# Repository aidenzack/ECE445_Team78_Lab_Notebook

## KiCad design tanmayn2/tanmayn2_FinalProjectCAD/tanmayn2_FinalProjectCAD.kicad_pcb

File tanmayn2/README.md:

## **Tanmay's Worklog**

### Week of 2026-02-18 - System Architecture Layout
Early planning of our system established design constraints we wanted to stick to, such as 
having 2 seperate USB-C connections:
- MCU (Arduino Nano ESP32) for 5V power and UART connection
- Battery Charging as part of our custom power management system to produce 3.3V power for peripherals

Which IMU we went with was based on high precision, tolerance for high-speed (up to 2000 degrees/sec motions) and force,
and SPI communication. This led us to choosing the:

**Adafruit TDK InvenSense ICM-20948 IMU**

Synchronization across all 4 sensors (Placed at the wrist, elbow, hip, and knee to capture the full kinematic chain) is key so we intend
to set up an FSYNC, with our fall back being that we can increase our sampling rate.

**Timing Analysis:**

- With a sampling rate of 200 Hz, we have a period _T_ = 5 ms.
- Our IMUs have an approximate read time of ~0.1ms
- Even during the fastest movements such as a wrist flick (~30 ms), we can capture 5-6 samples and grab precise data.

### Weeks of 2026-02-25 & 2026-03-02 - Full PCB Schematic Finalized + 1st Round PCB Ordered

I completed the first revision of our PCB Schematic and design, involving the following components:

- USB-C Receptacle (Power Input)
- Charger + Power Path IC (BQ24074RGT)
- 3.3V, 500mA LDO (TLV75533PDBVR)
- Arduino Nano ESP32
- Headers for Li-Po battery, IMUs
- LEDs for Debugging
- Designed 8-pin JST-style connectors for each IMU
- Implemented:
  - **Series resistors (22–47 Ω)** on SPI lines
  - **ESD protection** at connectors
  - **Local decoupling** at each connector

***PCB Schematic (Revision A)***

After the PCB Design Review, we talked with our TA about whether or not we are allowed to implement the full Arduino Nano ESP32 devboard or only allowed to use the chip.

Result - Allowed to use full Arduino Nano ESP32 Dev Board (w/ USB-C port, RESET button). Our PCB will be designed as expansion board for the MCU

---

### Week of 2026-03-08 - Tolerance Analysis of SPI Bus and Cable Delay

### SPI Throughput & Utilization Analysis

_Assumptions_

- 4 IMUs (wrist, elbow, hip, knee)
- Sampling rate: **220 Hz**
- Data per sample:
  - Accelerometer: 6 bytes
  - Gyroscope: 6 bytes
  - Register overhead: 1 byte

**Total per sample:**

```
13 bytes / sample / IMU
```

### Total Data Rate

```
13 bytes × 4 IMUs × 220 Hz = 11,400 bytes/s
11,440 × 8                  = 91,520 bits/s
```

### SPI Bus Capacity (2 MHz)

```
2,000,000 bits/s ÷ 8 = 250,000 bytes/s
```

### Bus Utilization

```
91,520 / 2,000,000 = 4.576%
```

### Interpretation

- Only **~4.576%** SPI bus utilization
- System is far from bandwidth-limited
- Allows operation at a **reduced SPI clock for robustness**

### SPI Timing & Cable Delay Analysis

### SPI Clock

Selected SPI clock: **2 MHz**

```
T            = 1 / 2 MHz = 500 ns
Half-cycle   = 250 ns
```

### Cable Length Estimates

| Sensor | Length (m) |
| :----- | :--------- |
| Wrist  | 1.00       |
| Elbow  | 0.45       |
| Hip    | 0.60       |
| Knee   | 0.90       |

### Propagation Delay (≈ 5 ns/m)

**One-way delay:**

```
t_pd = 5 ns/m × L
```

| Sensor | Delay (ns) |
| :----- | :--------- |
| Wrist  | 5.00       |
| Elbow  | 2.25       |
| Hip    | 3.00       |
| Knee   | 4.50       |

**Round-trip delay:**

```
t_rt ≈ 2 × t_pd
```

| Sensor | Delay (ns) |
| :----- | :--------- |
| Wrist  | 10.0       |
| Elbow  | 4.5        |
| Hip    | 6.0        |
| Knee   | 9.0        |

### Timing Comparison (Worst Case — Wrist)

```
One-way    : 5 ns  / 250 ns = 2.0%
Round-trip : 10 ns / 250 ns = 4.0%
```

### Interpretation

- Cable delay is **small relative to the SPI timing budget**
- 2 MHz provides **comfortable timing margin**
- System remains robust despite off-board wiring

---
## Week of 2026-03-08 - Testing and Validation
 
The entire signal chain was validated on a breadboard. This allowed us to verify SPI bus integrity and IMU synchronization in parallel with PCB fabrication.
 
### Breadboard Setup
 
The breadboard mirrors the central PCB topology:
 
- 1 × Arduino Nano ESP32 (MCU)
- 4 × ICM-20948 IMU breakout boards (wrist, elbow, hip, knee positions)
- Shared SPI bus: `SCLK`, `MOSI`, `MISO`
- Independent `CS_<IMU>` lines per IMU
- Shared `FSYNC` line (driven directly at 3.3 V on breadboard for testing)
> Built in collaboration with my teammate's Arduino firmware to read all 4 IMUs across the shared SPI bus.

**_Breadboard Setup_**

### Test 1 — SPI Bus Synchronization
 
**Goal:** Verify that the MCU correctly reads all 4 IMUs across the shared SPI bus within a single sampling frame, and that each IMU is uniquely identifiable via its `CS` line.
 
**Method:** Since all 4 IMUs are physically located on the same plane on the breadboard, their accelerometer and gyroscope readings should be **closely aligned** at any given instant — both at rest and under shared motion.

**_Breadboard Setup at Rest_**

**_Breadboard Setup in Motion_**

- The `Δ` values represent **sequential read delay** on the SPI bus, **not** sampling-time difference between IMUs.

### Test 2 — FSYNC Clock Alignment
 
**Goal:** Verify that the shared `FSYNC` line successfully aligns the internal sampling clocks of all 4 IMUs to a common reference.
 
**Method:** The firmware waits for the data-ready condition on all 4 IMUs, then assigns a shared frame number. By tracking the **frame index of peak motion** for each IMU, we can detect whether the IMUs' internal clocks are drifting independently or marching in lockstep.
 
**Before FSYNC Trigger (at rest, clocks free-running):**

> Peak-motion frames are **scattered** across IMU1=1, IMU2=32, IMU3=72, IMU4=34 — the internal sampling clocks are running independently.
 
**After FSYNC Trigger (sharp flick of breadboard provides impulse):**

> All 4 IMUs report peak motion at the **same frame index (2266)** — the FSYNC impulse successfully aligned their internal clocks.
---
## Week of 2026-03-23 - PCB Revisions

At the onset of delivery of our 1st Round PCB order, several issues were identified that required revisions before fabrication of our final design.
 
### Battery Connector Footprint Mismatch
 
- **Issue:** The Adafruit 3.7 V 1200 mAh Li-Po battery ships with **JST-PH 2.00 mm** connectors.
- **Original footprint:** Molex KK-254 **2.54 mm** male headers.
- **Resolution:** Updated the Li-Po battery connector footprint on the PCB to match JST-PH 2.00 mm.
### Trace Width Revisions for Power Signals
 
Several power-carrying traces needed to be widened to safely handle higher current loads:
 
| Signal      | Path                              | Old Width | New Width |
| :---------- | :-------------------------------- | :-------- | :-------- |
| `VDD5V`     | USB-C input → Charger IC          | 10 mils   | 20 mils   |
| `VBAT`      | Charger IC → Li-Po battery        | 10 mils   | 20 mils   |
| `+3V3_MAIN` | LDO → 4 IMUs + debugging LED      | 10 mils   | 20 mils   |

### FSYNC Logic-Level Mismatch
 
**Issue:** Per the Adafruit TDK InvenSense **ICM-20948** datasheet, the `FSYNC` pin requires an approximate **1.8 V** logic input. However, the Arduino Nano ESP32's `FSYNC` GPIO drives at **3.3 V**, ruling out a direct connection.
 
**Resolution:** Designed a **resistor voltage divider** to step down the 3.3 V signal to ~1.8 V before feeding it to the IMUs.

Used Resistors 2.2kΩ and 1.91kΩ as per ECE Shop availability

**Calculation:**
```
FSYNC_B = 3.3 V
 
FSYNC = FSYNC_B × ( 2.2 kΩ / (1.91 kΩ + 2.2 kΩ) )
      = 3.3 V × (2.2 / 1.91 + 2.2)
      = 1.767 V ~ 1.8V
```

**_Resistor Network for Stepdown to FSYNC_**

**_FINALIZED PCB DESIGN_**

---

## Week of 2026-03-30 - Initial Python Implementation

- Set up Python implementation via Spyder to process serial SPI data, set up initial zero calibration, capture accelerometer and gyroscope data from all 4 IMUs using hard triggers (START, STOP), and plot accelerometer and gyroscope data across all axes and for the IMU of the user's choosing.
- Extended and expanded upon heading into the week of 2026-04-06 in preparation for Progress Demo

---

## Week of 2026-04-06 - Progress Demo

- Set up end-to-end implementation from validating IMU connection to microcontroller via a healthy SPI bus, performed zero-calibration and proving effects of FSYNC on sample collection, and post-processing and data depiction through our Spyder implementation.
- Professor Joohyung Kim approved of the software backend and expected us to expand on it for interpretability and ease of operation, yet wanted to ensure our final on-body implementation can ensure the same functionality, especially with cable runs and promoting signal integrity to/from IMUs.

---

## Week of 2026-04-13 - Begin PCB Soldering

- With our finalized PCB finally delivered and our software implementation in a good spot, we began soldering our PCB. We used the oven to solder on most of the components, aside from the connectors, and afterwards, verified trace connections by using the continuity function on the multimeter
- Certain adjustments needed to be made. For instance, the ENABLE pin of the LDO was currently floating due to a mistake we made on the tracing side. We fixed this by soldering on a breadboard wire and tying the VSYS signal to the ENABLE pin, bringing it up to HIGH whenever the system is on and ensuring our LDO is actually working.
- Another issue was where our USB-C was positioned on our board. We realized we needed to cut out part of the ground plane and create a notch for the USB-C cable to connect through. After working with the machine shop, we got it fixed.
- From here, we wanted to check signal integrity from the PCB to the off-board IMUs via continuity mode and voltage readings when powered on.

**_PCB Probing_**

---

## Week of 2026-04-20 - Mock Demo + Presentation

- After finalizing PCB functionality and set up cable connections to IMUs, we set out to finalize on-body implementation and refine our software. We did the following:
  - CAD'ed and 3D-printed enclosures for the PCB and IMUs
  - Crafted straps for IMUs to sit on and to wear on the body
  - Crafted chest brace for PCB
  - Connected the entire PCB-IMU system to one of our teammates (Arjun)
  - Switched our Python implementation over to Dash Plotly
  - Implemented trigger-based Start (knee dip) and Stop (Wrist flick) shot capture mechanic into Python code

 **_UI Dashboard_**

- Mingrui (TA) informed us that while everything looks good, we need to focus on implementing feedback and figure out that soon, as that is one of the more significant components of our project

---

## Week of 2026-04-27 - Final Demo + Presentation

- All components from last week were improved upon for greater functionality and security. This includes the following:
  - Changed from exposed, Dupont terminal crimp pins to 2.54mm pitch connector metal terminals and KF2510 housing connector for better functionality
  - Bolstered straps for IMUs and PCB to be less constricting yet more secure
  - **Implemented Feedback Mechanism into UI Dashboard**
    - Implemented High Pass Filter + Notch Filter to suppress noise over cable runs and strengthen integrity
    - Extracts peak gyroscope and accelerometer metrics along with timings between IMU peaks
    - Calculates over normal distribution in comparison to the success profile and assigns a "severity" score as to which issue is best to focus on

  - Added Shot Label Status with line of feedback, FG%, Last 20 Shots Improvement, and plot controls

---

## Final Demo Reflection

Overall, a solid implementation that represents what we aimed to do.

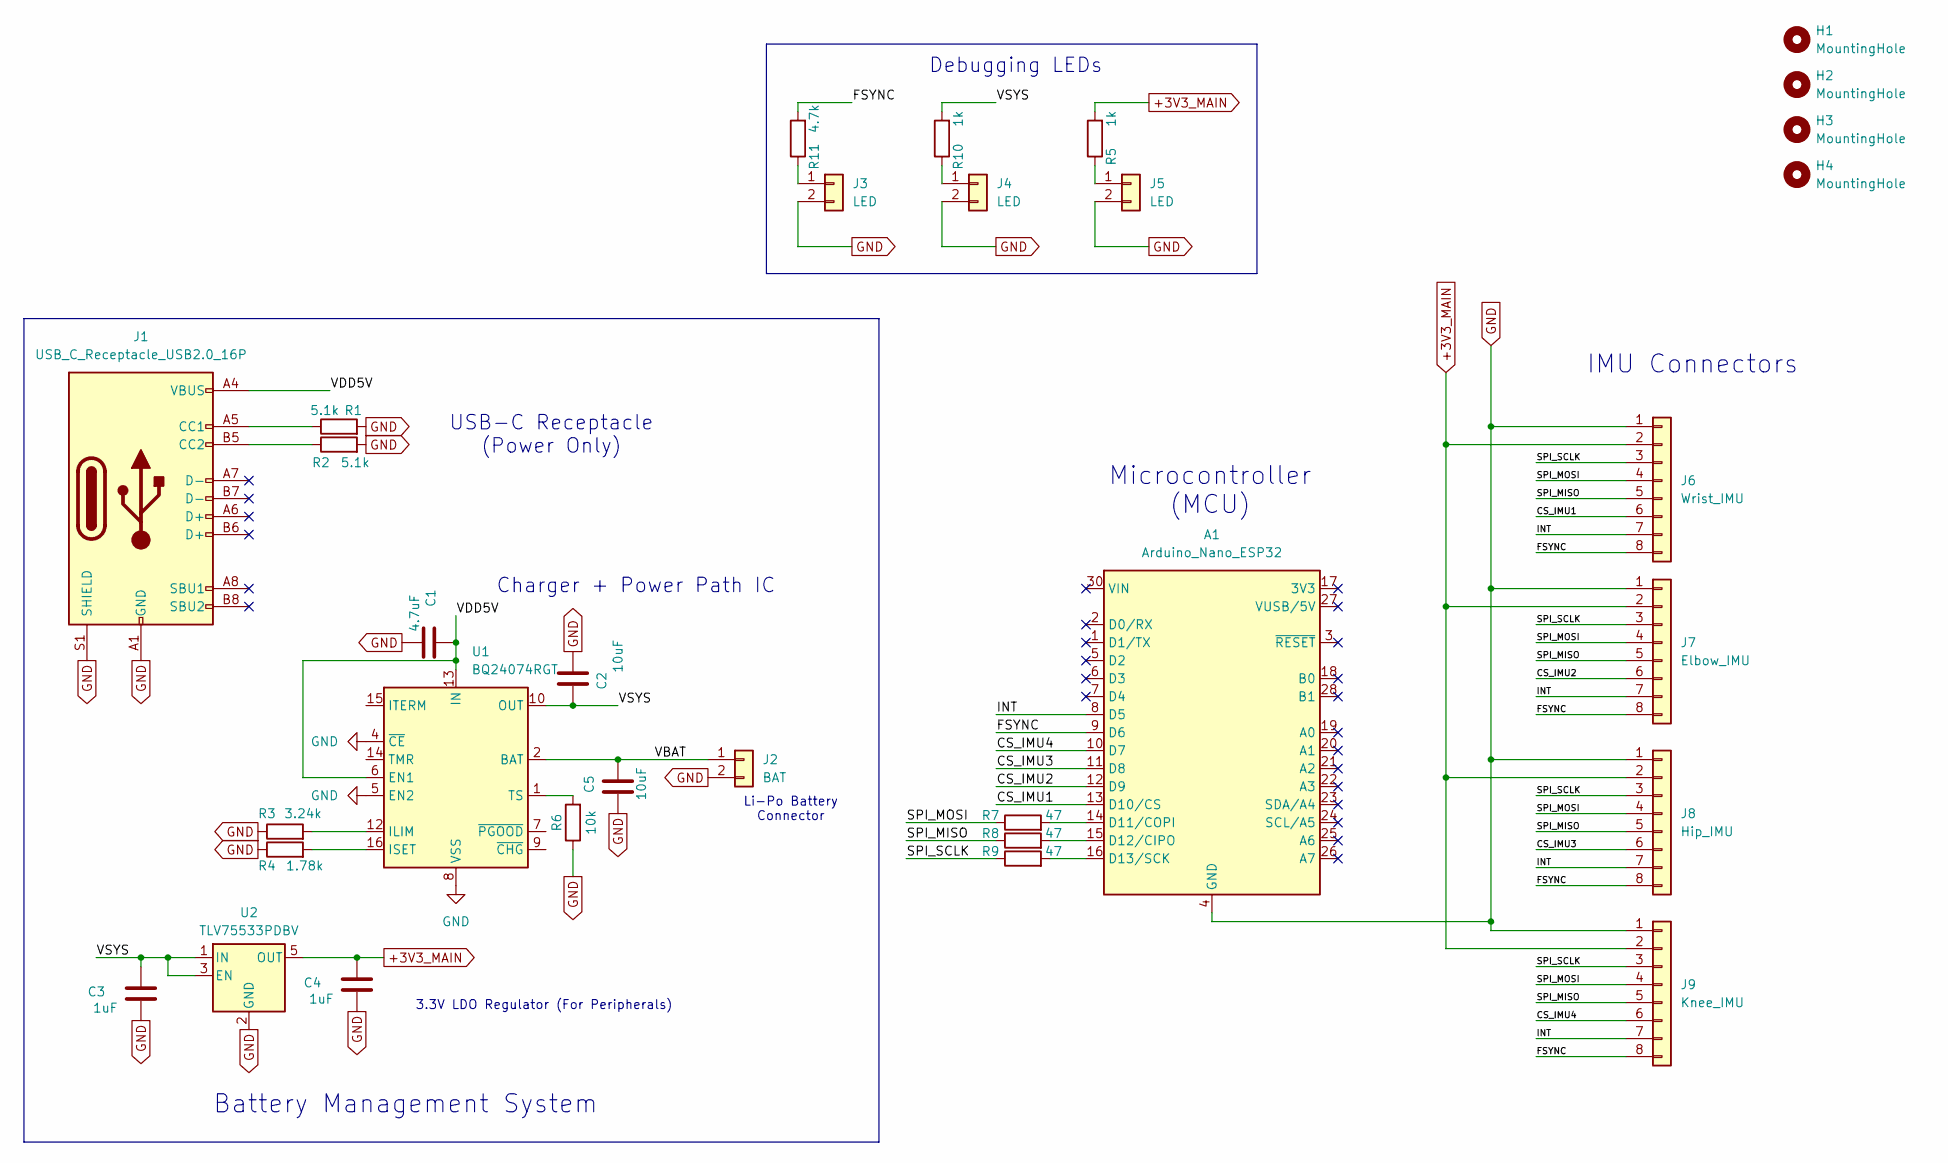
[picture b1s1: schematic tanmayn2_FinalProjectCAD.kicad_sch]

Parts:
A1: Arduino_Nano_ESP32; Arduino_Nano
C1: 4.7uF; C_0805_2012Metric_Pad1.18x1.45mm_HandSolder
C2, C5: 10uF; C_0805_2012Metric_Pad1.18x1.45mm_HandSolder
C3, C4: 1uF; C_0805_2012Metric_Pad1.18x1.45mm_HandSolder
H1, H2, H3, H4: MountingHole; MountingHole_3.2mm_M3
J1: USB_C_Receptacle_USB2.0_16P; USB_C_Receptacle_Molex_105450-0101
J2: BAT; Molex_KK-254_AE-6410-02A_1x02_P2.54mm_Vertical
J3, J4, J5: LED; Molex_KK-254_AE-6410-02A_1x02_P2.54mm_Vertical
J6: Wrist_IMU; Molex_KK-254_AE-6410-08A_1x08_P2.54mm_Vertical
J7: Elbow_IMU; Molex_KK-254_AE-6410-08A_1x08_P2.54mm_Vertical
J8: Hip_IMU; Molex_KK-254_AE-6410-08A_1x08_P2.54mm_Vertical
J9: Knee_IMU; Molex_KK-254_AE-6410-08A_1x08_P2.54mm_Vertical
R1, R2: 5.1k; R_0805_2012Metric_Pad1.20x1.40mm_HandSolder
R3: 3.24k; R_0805_2012Metric_Pad1.20x1.40mm_HandSolder
R4: 1.78k; R_0805_2012Metric_Pad1.20x1.40mm_HandSolder
R5, R10: 1k; R_0805_2012Metric_Pad1.20x1.40mm_HandSolder
R6: 10k; R_0805_2012Metric_Pad1.20x1.40mm_HandSolder
R7, R8, R9: 47; R_0805_2012Metric_Pad1.20x1.40mm_HandSolder
R11: 4.7k; R_0805_2012Metric_Pad1.20x1.40mm_HandSolder
U1: BQ24074RGT; VQFN-16-1EP_3x3mm_P0.5mm_EP1.6x1.6mm
U2: TLV75533PDBV; SOT-23-5

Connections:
+3V3_MAIN: C4.1, J6.2, J7.2, J8.2, J9.2, R5.2, U2.5 (OUT)
/CS_IMU1: A1.13 (D10/CS), J6.6
/CS_IMU2: A1.12 (D9), J7.6
/CS_IMU3: A1.11 (D8), J8.6
/CS_IMU4: A1.10 (D7), J9.6
/FSYNC: A1.9 (D6), J6.8, J7.8, J8.8, J9.8, R11.2
/INT: A1.8 (D5), J6.7, J7.7, J8.7, J9.7
/SPI_MISO: J6.5, J7.5, J8.5, J9.5, R8.1
/SPI_MOSI: J6.4, J7.4, J8.4, J9.4, R7.1
/SPI_SCLK: J6.3, J7.3, J8.3, J9.3, R9.1
/VBAT: C5.1, J2.1, U1.2 (BAT), U1.3 (BAT)
/VDD5V: C1.1, J1.A4 (VBUS), J1.A9 (VBUS), J1.B4 (VBUS), J1.B9 (VBUS), U1.6 (EN1), U1.13 (IN)
/VSYS: C2.1, C3.1, R10.2, U1.10 (OUT), U1.11 (OUT), U2.1 (IN), U2.3 (EN)
GND: A1.4 (GND), A1.29 (GND), C1.2, C2.2, C3.2, C4.2, C5.2, J1.A1 (GND), J1.A12 (GND), J1.B1 (GND), J1.B12 (GND), J1.S1 (SHIELD), J2.2, J3.2, J4.2, J5.2, J6.1, J7.1, J8.1, J9.1, R1.2, R2.2, R3.1, R4.1, R6.1, U1.4 (~CE), U1.5 (EN2), U1.8 (VSS), U1.17 (VSS), U2.2 (GND)
unnamed: A1.14 (D11/COPI), R7.2
unnamed: A1.15 (D12/CIPO), R8.2
unnamed: A1.16 (D13/SCK), R9.2
unnamed: J1.A5 (CC1), R1.1
unnamed: J1.B5 (CC2), R2.1
unnamed: J3.1, R11.1
unnamed: J4.1, R10.1
unnamed: J5.1, R5.1
unnamed: R3.2, U1.12 (ILIM)
unnamed: R4.2, U1.16 (ISET)
unnamed: R6.2, U1.1 (TS)

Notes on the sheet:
3.3V LDO Regulator (For Peripherals)
Li-Po Battery Connector
Charger + Power Path IC
IMU Connectors
USB-C Receptacle (Power Only)
Debugging LEDs
Microcontroller (MCU)
Battery Management System

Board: 2 copper layers, 32 parts (0 on the bottom side), 25 nets, no tracks yet.

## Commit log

2026-02-18 Initializing Lab Notebooks
2026-02-19 Create 2-19 Notes
2026-02-20 PCB Design Draft 2-19
2026-05-06 submitting notebook
2026-05-06 fixing images - notebook submitted
